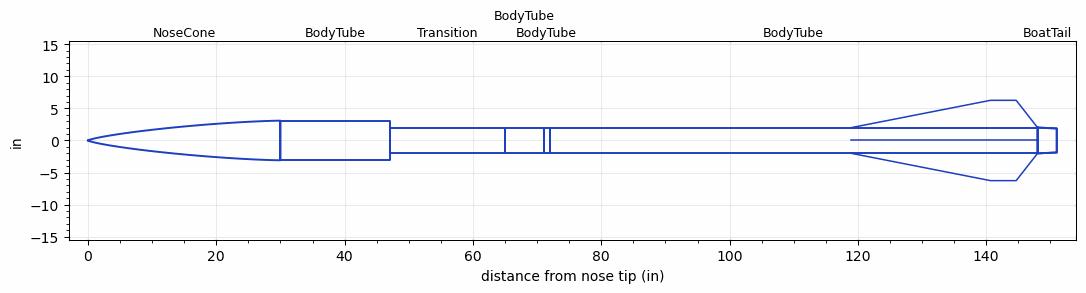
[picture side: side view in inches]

<RASAeroDocument>
 <FileVersion>2</FileVersion>
 <RocketDesign>
  <NoseCone>
   <Length>30</Length>
   <Diameter>6.17</Diameter>
   <Shape>Von Karman Ogive</Shape>
   <Location>0</Location>
  </NoseCone>
  <BodyTube>
   <Length>17</Length>
   <Diameter>6.17</Diameter>
   <Location>30</Location>
  </BodyTube>
  <Transition>
   <Length>18</Length>
   <Diameter>4.02</Diameter>
   <Location>47</Location>
   <RearDiameter>4.02</RearDiameter>
  </Transition>
  <BodyTube>
   <Length>6</Length>
   <Diameter>4.02</Diameter>
   <Location>65</Location>
  </BodyTube>
  <BodyTube>
   <Length>1</Length>
   <Diameter>4.02</Diameter>
   <Location>71</Location>
  </BodyTube>
  <BodyTube>
   <Length>76</Length>
   <Diameter>4.02</Diameter>
   <RailGuideDiameter>0.63</RailGuideDiameter>
   <RailGuideHeight>0.44</RailGuideHeight>
   <Location>72</Location>
   <BoattailLength>3</BoattailLength>
   <BoattailRearDiameter>3.75</BoattailRearDiameter>
   <Fin>
    <Count>4</Count>
    <Chord>29</Chord>
    <Span>4.25</Span>
    <SweepDistance>21.672</SweepDistance>
    <TipChord>4</TipChord>
    <Thickness>0.25</Thickness>
    <Location>29</Location>
    <AirfoilSection>Rounded</AirfoilSection>
   </Fin>
  </BodyTube>
  <BoatTail>
   <Length>3</Length>
   <Diameter>4.02</Diameter>
   <RearDiameter>3.75</RearDiameter>
   <Location>148</Location>
  </BoatTail>
  <Surface>Smooth Paint</Surface>
  <ModifiedBarrowman>False</ModifiedBarrowman>
  <Turbulence>False</Turbulence>
  <UseBooster1>False</UseBooster1>
  <UseBooster2>False</UseBooster2>
 </RocketDesign>
 <LaunchSite>
  <Altitude>4595</Altitude>
  <Pressure>30.09</Pressure>
  <RodAngle>0</RodAngle>
  <RodLength>17</RodLength>
  <Temperature>110</Temperature>
  <WindSpeed>5</WindSpeed>
 </LaunchSite>
 <Recovery>
  <Altitude1>1000</Altitude1>
  <Altitude2>1000</Altitude2>
  <DeviceType1>Parachute</DeviceType1>
  <DeviceType2>Parachute</DeviceType2>
  <Event1>True</Event1>
  <Event2>True</Event2>
  <Size1>48</Size1>
  <Size2>144</Size2>
  <EventType1>Apogee</EventType1>
  <EventType2>Altitude</EventType2>
  <CD1>2.2</CD1>
  <CD2>2.2</CD2>
 </Recovery>
 <SimulationList>
  <Simulation>
   <SustainerEngine>N4000  (Aerotech)</SustainerEngine>
   <SustainerLaunchWt>66.8</SustainerLaunchWt>
   <SustainerNozzleDiameter>3.5</SustainerNozzleDiameter>
   <SustainerCG>92.87</SustainerCG>
   <SustainerIgnitionDelay>0</SustainerIgnitionDelay>
   <Booster1SeparationDelay>0</Booster1SeparationDelay>
   <Booster1IgnitionDelay>0</Booster1IgnitionDelay>
   <IncludeBooster1>False</IncludeBooster1>
   <Booster2Delay>0</Booster2Delay>
   <IncludeBooster2>False</IncludeBooster2>
   <TimetoApogee>39.87931</TimetoApogee>
   <MaxAltitude>30068.01</MaxAltitude>
   <MaxVelocity>2017.308</MaxVelocity>
  </Simulation>
 </SimulationList>
</RASAeroDocument>
